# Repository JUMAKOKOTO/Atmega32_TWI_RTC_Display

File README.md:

# Atmega32_TWI_RTC_Display
ATmega32 RTC Display PBL Project

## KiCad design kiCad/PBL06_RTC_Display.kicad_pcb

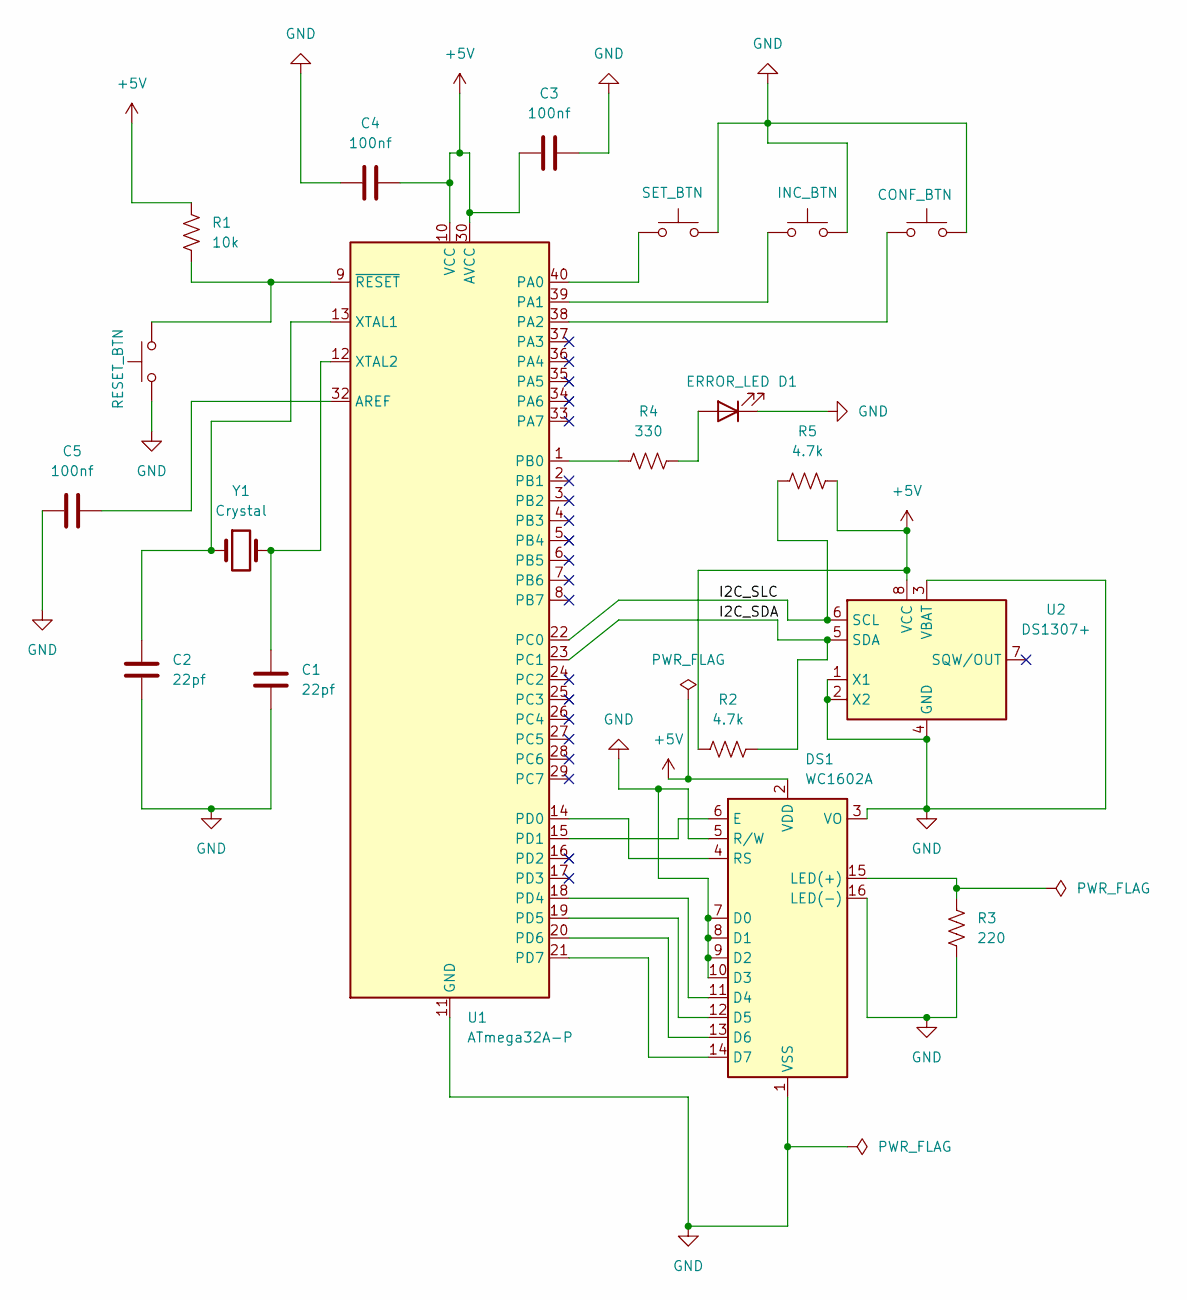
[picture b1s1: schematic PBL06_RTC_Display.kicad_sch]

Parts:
C1, C2: 22pf; C_Disc_D5.0mm_W2.5mm_P2.50mm
C3, C4, C5: 100nf; C_Disc_D5.0mm_W2.5mm_P2.50mm
D1: ERROR_LED; LED_D5.0mm
DS1: WC1602A
R1: 10k; R_Axial_DIN0207_L6.3mm_D2.5mm_P10.16mm_Horizontal
R2, R5: 4.7k; R_Axial_DIN0207_L6.3mm_D2.5mm_P10.16mm_Horizontal
R3: 220; R_Axial_DIN0207_L6.3mm_D2.5mm_P10.16mm_Horizontal
R4: 330; R_Axial_DIN0207_L6.3mm_D2.5mm_P10.16mm_Horizontal
SW1: SET_BTN; SW_PUSH_6mm
SW2: INC_BTN; SW_PUSH_6mm
SW3: CONF_BTN; SW_PUSH_6mm
SW4: RESET_BTN; SW_PUSH_6mm
U1: ATmega32A-P; DIP-40_W15.24mm
U2: DS1307+; DIP-8_W7.62mm
Y1: Crystal; Crystal_HC49-4H_Vertical

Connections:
+5V: C3.1, C4.2, DS1.2 (VDD), R1.1, R2.2, R5.2, U1.10 (VCC), U1.30 (AVCC), U2.8 (VCC)
/I2C_SDA: R2.1, U1.23 (PC1), U2.5 (SDA)
/I2C_SLC: R5.1, U1.22 (PC0), U2.6 (SCL)
GND: C1.2, C2.2, C3.2, C4.1, C5.1, D1.1 (K), DS1.1 (VSS), DS1.3 (VO), DS1.5 (R/W), DS1.7 (D0), DS1.8 (D1), DS1.9 (D2), DS1.10 (D3), DS1.16 (LED(-)), R3.2, SW1.2, SW2.2, SW3.2, SW4.1, U1.11 (GND), U1.31 (GND), U2.1 (X1), U2.2 (X2), U2.3 (VBAT), U2.4 (GND)
unnamed: D1.2 (A), R4.2
unnamed: DS1.11 (D4), U1.18 (PD4)
unnamed: DS1.12 (D5), U1.19 (PD5)
unnamed: DS1.13 (D6), U1.20 (PD6)
unnamed: DS1.14 (D7), U1.21 (PD7)
unnamed: DS1.6 (E), U1.15 (PD1)
unnamed: DS1.15 (LED(+)), R3.1
unnamed: DS1.4 (RS), U1.14 (PD0)
unnamed: C5.2, U1.32 (AREF)
unnamed: SW1.1, U1.40 (PA0)
unnamed: SW2.1, U1.39 (PA1)
unnamed: SW3.1, U1.38 (PA2)
unnamed: R4.1, U1.1 (PB0)
unnamed: C2.1, U1.13 (XTAL1), Y1.1
unnamed: C1.1, U1.12 (XTAL2), Y1.2
unnamed: R1.2, SW4.2, U1.9 (~RESET)

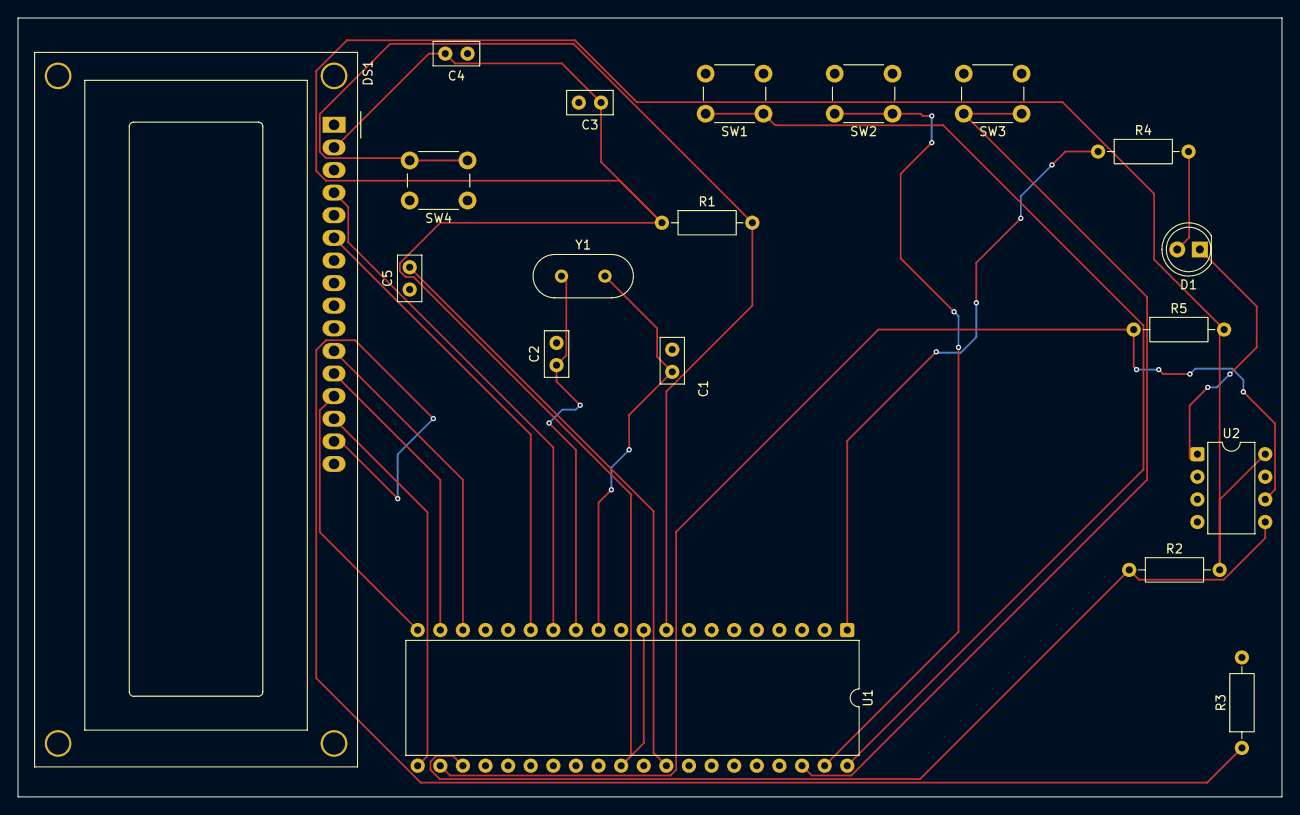
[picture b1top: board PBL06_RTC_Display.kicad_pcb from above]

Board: 2 copper layers, 142.0 x 87.5 mm, 19 parts (0 on the bottom side), 20 nets.

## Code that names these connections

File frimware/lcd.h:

// #ifndef LCD_H
// #define LCD_H

// #include <avr/io.h>
// #include <util/delay.h>

// #define LCD_RS PD0
// #define LCD_EN PD1

// void LCD_Init(void);
// void LCD_Command(uint8_t cmd);
// void LCD_Char(char data);
// void LCD_String(char *str);
// void LCD_Clear(void);
// void LCD_Goto(uint8_t row,uint8_t col);
// void LCD_Integer(int value);

// #endif




#ifndef LCD_H
#define LCD_H

#ifndef F_CPU
#define F_CPU 8000000UL
#endif

#include <avr/io.h>
#include <util/delay.h>
#include <stdint.h>

/****************************************************
                LCD CONNECTION
*****************************************************

ATmega32          LCD

PD0 ------------> RS
PD1 ------------> EN
PD4 ------------> D4
PD5 ------------> D5
PD6 ------------> D6
PD7 ------------> D7

RW -------------- GND

****************************************************/

#define LCD_RS     PD0
#define LCD_EN     PD1

/****************************************************
                LCD FUNCTIONS
****************************************************/

void LCD_Init(void);

void LCD_Command(uint8_t cmd);

void LCD_Char(char data);

void LCD_String(const char *str);

void LCD_Clear(void);

void LCD_Goto(uint8_t row, uint8_t col);

void LCD_Integer(int value);

#endif

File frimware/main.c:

#ifndef F_CPU
#define F_CPU 8000000UL
#endif

#include <avr/io.h>
#include <util/delay.h>
#include <stdio.h>

#include "lcd.h"
#include "rtc.h"

/***************************************************
                BUTTONS
****************************************************/
#define SET_BTN     PA0
#define INC_BTN     PA1
#define OK_BTN      PA2

/***************************************************
                ERROR LED
****************************************************/
#define ERROR_LED   PB0

RTC_Time rtc;

char lcdBuffer[17];

uint8_t editMode=0;
uint8_t editField=0;

/***************************************************
            BUTTON READ
****************************************************/
uint8_t ButtonPressed(uint8_t pin)
{
    if(!(PINA&(1<<pin)))
    {
        _delay_ms(20);

        if(!(PINA&(1<<pin)))
        {
            while(!(PINA&(1<<pin)));

            return 1;
        }
    }

    return 0;
}

/***************************************************
            SHOW CLOCK
****************************************************/
void DisplayClock(void)
{
    LCD_Clear();

    sprintf(lcdBuffer,"%02d:%02d:%02d",
            rtc.hour,
            rtc.minute,
            rtc.second);

    LCD_Goto(0,4);
    LCD_String(lcdBuffer);

    sprintf(lcdBuffer,"%02d/%02d/20%02d",
            rtc.date,
            rtc.month,
            rtc.year);

    LCD_Goto(1,2);
    LCD_String(lcdBuffer);
}

/***************************************************
            SHOW EDIT SCREEN
****************************************************/
void DisplayEdit(void)
{
    LCD_Clear();

    switch(editField)
    {
        case 0:
            LCD_String("SET HOURS");
            sprintf(lcdBuffer,"%02d",rtc.hour);
            break;

        case 1:
            LCD_String("SET MINUTES");
            sprintf(lcdBuffer,"%02d",rtc.minute);
            break;

        case 2:
            LCD_String("SET DATE");
            sprintf(lcdBuffer,"%02d",rtc.date);
            break;

        case 3:
            LCD_String("SET MONTH");
            sprintf(lcdBuffer,"%02d",rtc.month);
            break;

        case 4:
            LCD_String("SET YEAR");
            sprintf(lcdBuffer,"%02d",rtc.year);
            break;
    }

    LCD_Goto(1,7);
    LCD_String(lcdBuffer);
}

/***************************************************
                MAIN
****************************************************/
int main(void)
{

    DDRA &= ~((1<<SET_BTN)|
              (1<<INC_BTN)|
              (1<<OK_BTN));

    PORTA |= (1<<SET_BTN)|
             (1<<INC_BTN)|
             (1<<OK_BTN);

    DDRB |= (1<<ERROR_LED);

    PORTB &= ~(1<<ERROR_LED);

    LCD_Init();

    TWI_Init();

    LCD_Clear();
    LCD_String("RTC PROJECT");

    _delay_ms(1000);

    while(1)
    {

        if(RTC_Read(&rtc))
        {
            PORTB &= ~(1<<ERROR_LED);
        }
        else
        {
            PORTB |= (1<<ERROR_LED);

            LCD_Clear();
            LCD_String("RTC ERROR");

            _delay_ms(500);

            continue;
        }

        if(editMode==0)
        {
            DisplayClock();
        }
        else
        {
            DisplayEdit();
        }

//         /****************************************
//                 SET BUTTON
//         *****************************************/

//         if(ButtonPressed(SET_BTN))
//         {
//             editMode=1;

//             editField++;

//             if(editField>4)
//             {
//                 editField=0;
//             }
//         }

//         /****************************************
//                 INC BUTTON
//         *****************************************/

//         if(ButtonPressed(INC_BTN))
//         {

//             switch(editField)
//             {

//                 case 0:
//                     rtc.hour++;

//                     if(rtc.hour>=24)
//                         rtc.hour=0;
//                     break;

//                 case 1:
//                     rtc.minute++;

//                     if(rtc.minute>=60)
//                         rtc.minute=0;
//                     break;

//                 case 2:
//                     rtc.date++;

//                     if(rtc.date>31)
//                         rtc.date=1;
//                     break;

//                 case 3:
//                     rtc.month++;

//                     if(rtc.month>12)
//                         rtc.month=1;
//                     break;

//                 case 4:
//                     rtc.year++;

//                     if(rtc.year>99)
//                         rtc.year=0;
//                     break;
//             }

//         }

//         /****************************************
//                 CONFIRM BUTTON
//         *****************************************/

//         if(ButtonPressed(OK_BTN))
//         {

//             RTC_Write(&rtc);

//             editMode=0;

//             LCD_Clear();

//             LCD_String("TIME SAVED");

//             _delay_ms(700);

//         }

//         _delay_ms(200);

//     }

// }


        /****************************************
                SET BUTTON
        ****************************************/
        if(ButtonPressed(SET_BTN))
        {
            if(editMode == 0)
            {
                editMode = 1;
                editField = 0;
            }
            else
            {
                editField++;

                if(editField > 5)
                    editField = 0;
            }
        }

        /****************************************
                INCREMENT BUTTON
        ****************************************/
        if(ButtonPressed(INC_BTN))
        {
            if(editMode)
            {
                switch(editField)
                {
                    case 0:     // Hour
                        rtc.hour++;
                        if(rtc.hour >= 24)
                            rtc.hour = 0;
                        break;

                    case 1:     // Minute
                        rtc.minute++;
                        if(rtc.minute >= 60)
                            rtc.minute = 0;
                        break;

                    case 2:     // Second
                        rtc.second++;
                        if(rtc.second >= 60)
                            rtc.second = 0;
                        break;

                    case 3:     // Date
                        rtc.date++;
                        if(rtc.date > 31)
                            rtc.date = 1;
                        break;

                    case 4:     // Month
                        rtc.month++;
                        if(rtc.month > 12)
                            rtc.month = 1;
                        break;

                    case 5:     // Year
                        rtc.year++;
                        if(rtc.year > 99)
                            rtc.year = 0;
                        break;
                }

                DisplayEdit();
            }
        }

        /****************************************
                OK BUTTON
        ****************************************/
        if(ButtonPressed(OK_BTN))
        {
            if(editMode)
            {
                RTC_Write(&rtc);

                editMode = 0;

                LCD_Clear();
                LCD_String("TIME SAVED");

                _delay_ms(800);
            }
        }

        _delay_ms(150);
    }

    return 0;
}
